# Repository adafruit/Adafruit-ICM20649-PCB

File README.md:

## Adafruit ICM20649 Wide-Range 6-DoF IMU PCB

<a href="http://www.adafruit.com/products/4464"><br/>
Click here to purchase one from the Adafruit shop</a>

PCB files for the Adafruit ICM20649 Wide-Range 6-DoF IMU. 

Format is EagleCAD schematic and board layout
* https://www.adafruit.com/product/4464

### Description

INSERT PRODUCT COPY HERE

### License

Adafruit invests time and resources providing this open source design, please support Adafruit and open-source hardware by purchasing products from [Adafruit](https://www.adafruit.com)!

Designed by Limor Fried/Ladyada for Adafruit Industries.

Creative Commons Attribution/Share-Alike, all text above must be included in any redistribution. 
See license.txt for additional details.

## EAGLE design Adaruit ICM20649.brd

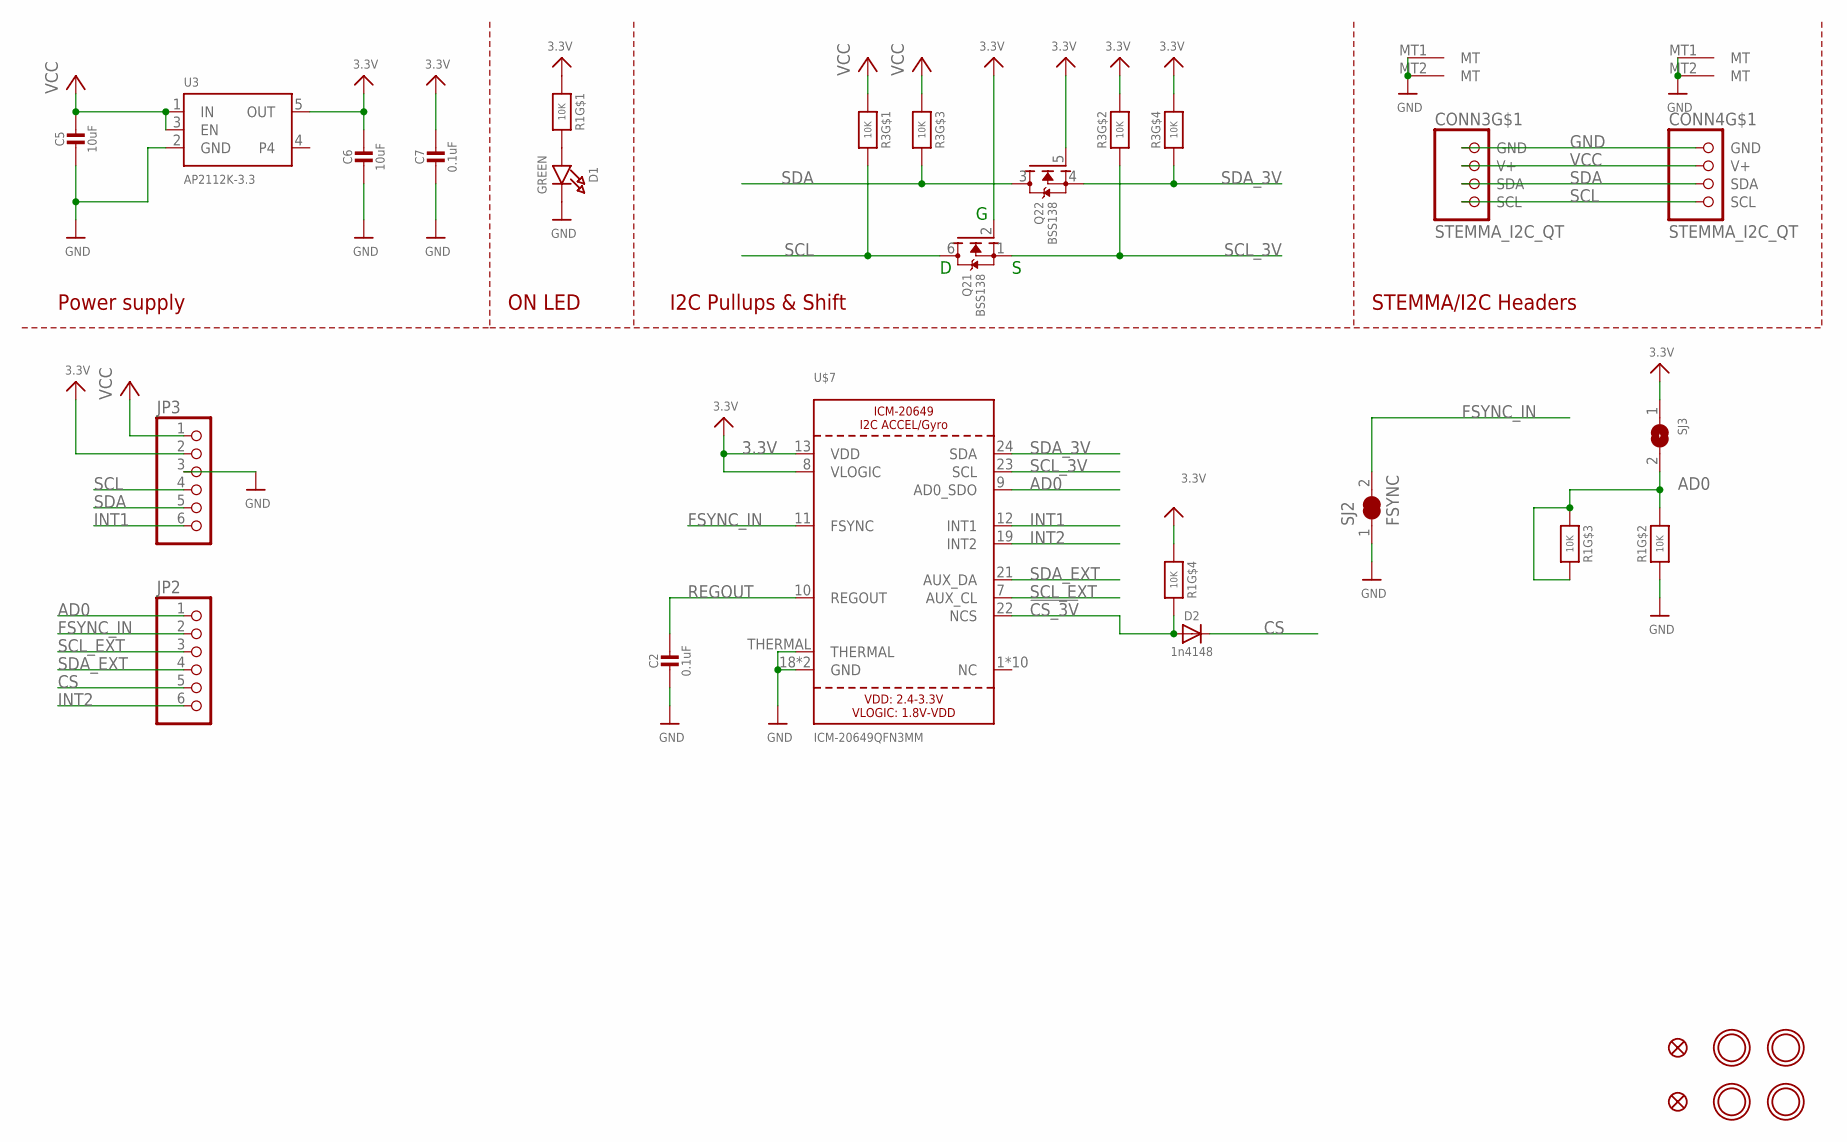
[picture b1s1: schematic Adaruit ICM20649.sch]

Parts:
C2, C7: 0.1uF; 0603-NO
C5, C6: 10uF; 0805-NO
CONN3, CONN4: STEMMA_I2C_QT; JST_SH4
D1: GREEN; CHIPLED_0603_NOOUTLINE
D2: 1n4148; SOD-323
FID3, FID4: FIDUCIAL_1MM
JP2: HEADER-1X6ROUND; 1X06_ROUND
JP3: HEADER-1X670MIL; 1X06_ROUND_70
Q2: BSS138; SOT363
R1, R3: 10K; RESPACK_4X0603
SJ2: FSYNC; SOLDERJUMPER_CLOSEDWIRE
SJ3: SOLDERJUMPER; SOLDERJUMPER_ARROW_NOPASTE
U3: AP2112K-3.3; SOT23-5
U$7: ICM-20649QFN3MM; QFN24_3MM
U$39, U$40, U$42, U$43: MOUNTINGHOLE2.5; MOUNTINGHOLE_2.5_PLATED

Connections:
3.3V: C6.1, C7.1, JP3.2, Q2.2 (G), Q2.5 (G), R1.1, R1.4 (1), R3.2 (1), R3.4 (1), SJ3.1, U3.5 (OUT), U$7.8 (VLOGIC), U$7.13 (VDD)
!CS_3V: D2.A, R1.5 (2), U$7.22 (NCS)
AD0: JP2.1, R1.3 (1), R1.6 (2), R1.7 (2), SJ3.2, U$7.9 (AD0_SDO)
CS: D2.C, JP2.5
FSYNC_IN: JP2.2, SJ2.2, U$7.11 (FSYNC)
GND: C2.2, C5.2, C6.2, C7.2, CONN3.1 (GND), CONN3.MT1 (MT), CONN3.MT2 (MT), CONN4.1 (GND), CONN4.MT1 (MT), CONN4.MT2 (MT), D1.C, JP3.3, R1.2 (1), SJ2.1, U3.2 (GND), U$7.18 (GND), U$7.20 (GND), U$7.THERMAL
INT1: JP3.6, U$7.12 (INT1)
INT2: JP2.6, U$7.19 (INT2)
unnamed: D1.A, R1.8 (2)
REGOUT: C2.1, U$7.10 (REGOUT)
SCL: CONN3.4 (SCL), CONN4.4 (SCL), JP3.4, Q2.6 (D), R3.8 (2)
SCL_3V: Q2.1 (S), R3.7 (2), U$7.23 (SCL)
SCL_EXT: JP2.3, U$7.7 (AUX_CL)
SDA: CONN3.3 (SDA), CONN4.3 (SDA), JP3.5, Q2.3 (D), R3.6 (2)
SDA_3V: Q2.4 (S), R3.5 (2), U$7.24 (SDA)
SDA_EXT: JP2.4, U$7.21 (AUX_DA)
VCC: C5.1, CONN3.2 (V+), CONN4.2 (V+), JP3.1, R3.1, R3.3 (1), U3.1 (IN), U3.3 (EN)

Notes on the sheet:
I2C Pullups & Shift
STEMMA/I2C Headers
ON LED
Power supply

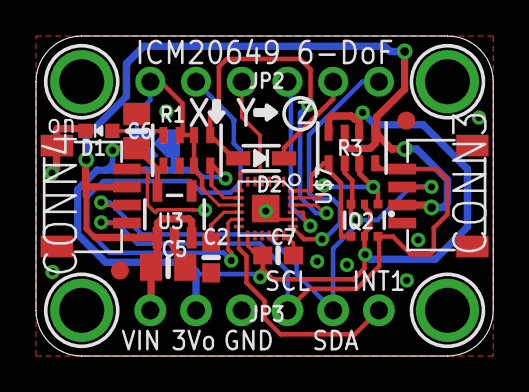
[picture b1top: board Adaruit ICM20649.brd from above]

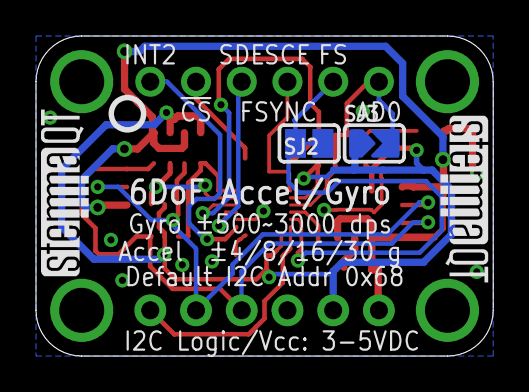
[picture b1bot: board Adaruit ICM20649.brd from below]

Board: 2 copper layers, 25.4 x 17.8 mm, 26 parts (5 on the bottom side), 17 nets.

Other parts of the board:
U$46: PCBFEAT-REV-040
U$47, U$48: STEMMAQT

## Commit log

2020-01-27 Initial commit, needs product copy
2020-09-07 Fixed product image

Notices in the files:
parts and their libraries:
microbuilder: This work is placed in the public domain, and may be freely used for commercial and non-commercial work with the following conditions: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
